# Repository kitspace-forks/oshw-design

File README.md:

###Open-source hardware design
----------

####Introduction

This repository will contain all the hardware designs by @kennethlimcp.

Temporary project name: **One oshw project per month**

The purpose is to encourage people to **embrace openness** and get more people **interested** in hardware design/hacking.

####Source-tree

Designs here are uploaded with the following document to **minimize friction** for a beginner to get started:

- Schematic design (EAGLE CAD)

- GERBER file      (fabricate PCB immediately)

- BOM list         (widely available parts + changelog)

- PDF capture      (learn without Schematic software)

- Datasheet        (easy reference without searching)

- Appnote          (deeper learning and understanding)

- Casing           (more user-friendly and safe to hold)

####Useful writeups (by me)

- [Bringing up a new board from scratch](/Resources/bring-up.md)
- [Checking a new PCB and populating it](/Resources/pcb-checks.md)
- [EAGLE start off and mistakes](/Resources/eagle-notes.md)

####Resources

- [Spark Proto2Prod website](http://www.proto2prod.com/)

- [EAGLE Help](http://web.mit.edu/xavid/arch/i386_rhel4/help/index.htm)

- [Sparkfun EAGLE Settings](https://github.com/sparkfun/SparkFun_Eagle_Settings)

- [3D Board viewer](http://3dbrdviewer.cytec.bg/)

- [KiCad Software](http://www.kicad-pcb.org/)

- [Systematic PCB verification](https://engineering.purdue.edu/ece477/Resources/SystematicPCBVerification.pdf)

- [7 fatal pcb mistakes to avoid by Make](http://makezine.com/2016/08/15/7-fatal-mistakes-avoid-printed-circuit-board-pcb-design/)

- [ Board Level
Electromagnetic Compatibility](http://www.nxp.com/files/microcontrollers/doc/app_note/AN2321.pdf)

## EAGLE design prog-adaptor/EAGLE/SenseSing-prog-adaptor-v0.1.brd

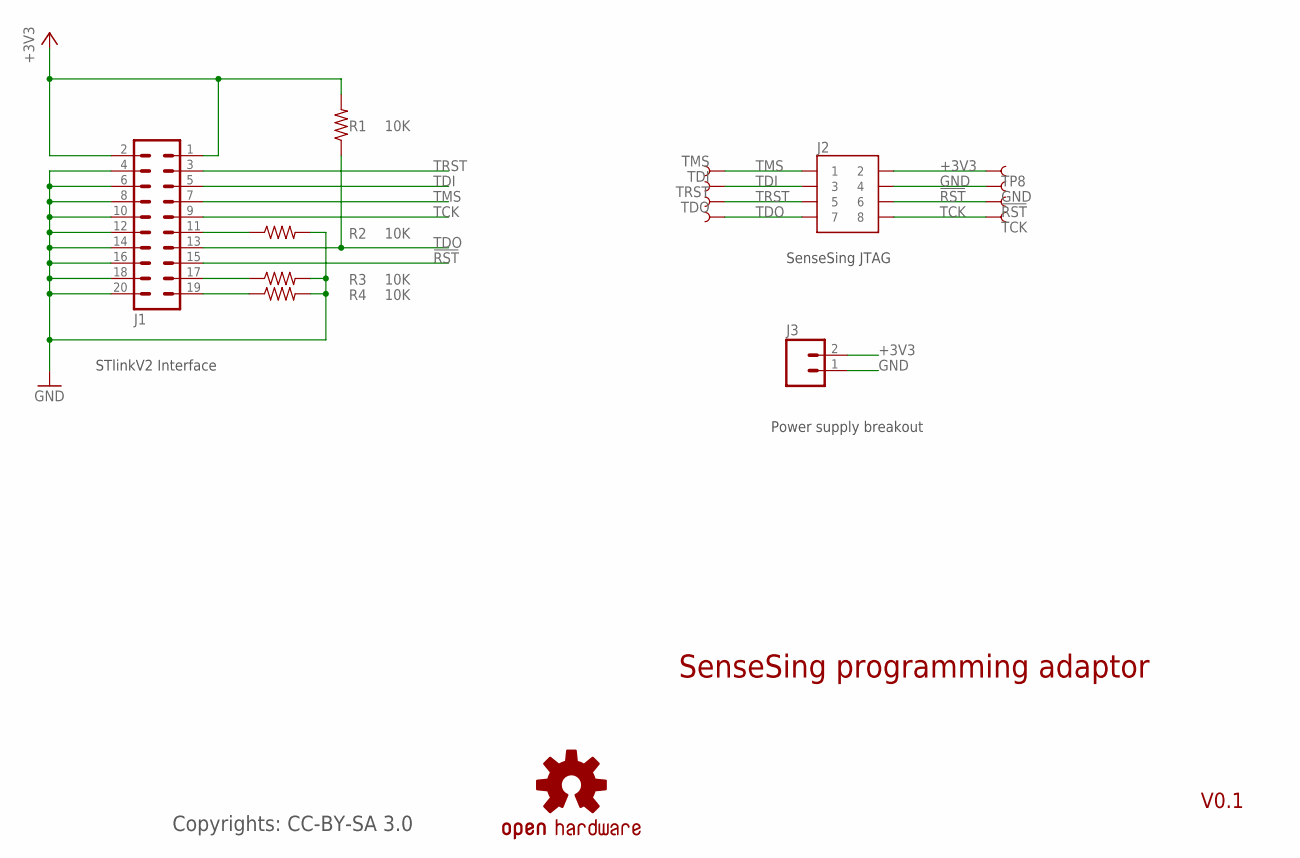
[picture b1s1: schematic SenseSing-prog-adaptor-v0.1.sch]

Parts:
!RST: TEST-POINT3; PAD.03X.03
GND: TEST-POINT3; PAD.03X.03
J1: ML20
J2: JTAG_CONNECTOR; JTAG_DIP
J3: M02PTH; 1X02
LOGO1: OSHW-LOGOPAD; OSHW-LOGO-M-PAD
R1, R2, R3, R4: 10K; AXIAL-0.3
TCK: TEST-POINT3; PAD.03X.03
TDI: TEST-POINT3; PAD.03X.03
TDO: TEST-POINT3; PAD.03X.03
TMS: TEST-POINT3; PAD.03X.03
TP8: TEST-POINT3; PAD.03X.03
TRST: TEST-POINT3; PAD.03X.03

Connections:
!RST: !RST.P$1, J1.15, J2.6
+3V3: J1.1, J1.2, J2.2, J3.2, R1.P$2 (2), TP8.P$1
GND: GND.P$1, J1.4, J1.6, J1.8, J1.10, J1.12, J1.14, J1.16, J1.18, J1.20, J2.4, J3.1, R2.P$2 (2), R3.P$2 (2), R4.P$2 (2)
unnamed: J1.19, R4.P$1 (1)
unnamed: J1.17, R3.P$1 (1)
unnamed: J1.11, R2.P$1 (1)
TCK: J1.9, J2.8, TCK.P$1
TDI: J1.5, J2.3, TDI.P$1
TDO: J1.13, J2.7, R1.P$1 (1), TDO.P$1
TMS: J1.7, J2.1, TMS.P$1
TRST: J1.3, J2.5, TRST.P$1

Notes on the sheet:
STlinkV2 Interface
SenseSing JTAG
SenseSing programming adaptor
Copyrights: CC-BY-SA 3.0
Power supply breakout

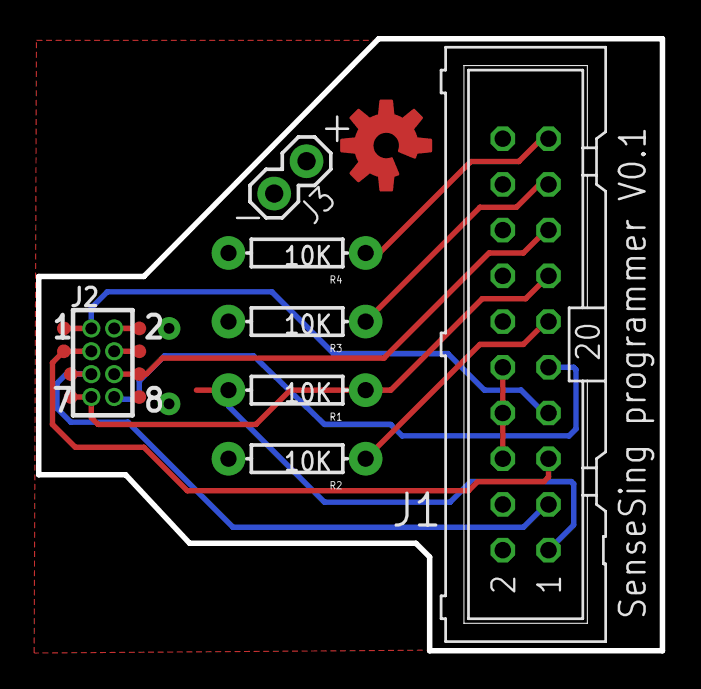
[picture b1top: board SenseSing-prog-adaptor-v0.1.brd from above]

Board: 4 copper layers, 34.7 x 34.0 mm, 16 parts (0 on the bottom side), 11 nets.

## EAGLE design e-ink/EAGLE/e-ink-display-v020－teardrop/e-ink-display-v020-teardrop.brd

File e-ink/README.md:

#Wifi E-ink display
----------

###Introduction

The main motivation for this device comes from the regular use of 16x2 or nokia old-style LCD display. They are nice but too small for a sizeable project that requires a simple but viewable display from a distance.

This also challenges me to try out FPC connector that i have never handled before and at the same time design an entire system comprising from power to display signal driver.

The current revision of **V0.0.3** does not work as the I2C GPIO expander is unable to toggle the control pins at `us` resolution so a re-design has to be done. **V0.1.0** is a WIP to improve **V0.0.2** but is only a WIP and is not a working board as well.

####Power system

- USB +5V or single cell Li-ion
- Battery charging and simultaneous system supply
- 3V3 buck converter for primary rail

#####Input options
- microB USB
- jumper wire (+ and -)

#####E-ink supply notes

A LT1945 DC/DC converter is powered by VBAT from the 1-cell li-ion battery to provide the +22V and -20V required for the Gate supply. The next power stage comprises of a simple LDO (LM78(79)/L15) to generate +15V and -15V for the Source supply. There's a LTSPICE file available in this repository that shows the performance of the LT1945 through simulation. This design comes from the datasheet and the components have been properly sized to have beefy ratings.

There are newer ICs in the market that handles the entire power generation required to drive an e-ink display and they should be utilized in the new revision if they can be bought easily in the market. Otherwise, replacing the LDOs might be a considering to achieve better low power consumption in sleep mode.

VDD and VSS supply for the e-ink is powered using a GPIO as the current draw (according to the notes) is only 1mA and this allows up to turn off the display for power saving.

The SMPS power input is controlled using a simple P-channel Mosfet load switch technique to cut off supply when it is not required.

#####Battery power management design

After much sourcing and finding a part available in the Chinese market, I found the BQ24075 suitable for the job that provides a good mix of features. This IC allows a maximum input voltage of 28V and comes with over-voltage protection! No external inductor is required (compared to BQ24260). There's also 2 status signal that allows the MCU to know if there's an external power source connected and whether the battery is currently charging. This allows us to change the "power mode" of the device with faster go-to-sleep timing when there is not power source attached.

This addition low-cost circuit footprint is added for variety. A MCP7381T is used to charge a single cell Li-ion and the VBAT is directly fed to the system. This, however, does not allow the system to be powered up if a battery is not present.

####Driver design notes

The e-ink display requires a fair bit of control pins and part of the reason is not fully understanding which pins are in use and necessary for driving. Therefore, to ensure a higher success rate during rev. 0.0.2, consideration is made to hook up all the exposed pins. Pins that are pulled high and low are also wired up with 0 ohm resistors for flexibility to test their purpose or change the pull voltage.

One design considered is to use 2 x 8 GPIO expander; one for the 8 bit data and another for the seldom toggled controls pins. There are 16 port GPIO expander in the market but having the data pins and control pins independent of each other during writes prevents accidental toggling of the incorrect pin that may result in a damaged display.

Another design is to use a separate MCU that connects directly to all the pins available but most of the Arduino options have low FLASH and RAM. The next notch up would result coding in C (MCU running some RTOS) which is too much to handle at this point in time.

The GPIO expander design is implemented for the initial rev to bring up the board with a Spark Core/Photon that is a beefier Arduino variant that allows us to avoid the low level path for now. Using an external MCU would definitely be a better path to take in future revisions. INT pins are not wired up as all the pins are used as OUTPUT.

####Peripherals

These are implemented in rev 0.0.2:

- Accelerometer to determine screen orientation
- Temperature sensor, duh
- microSD card

future considerations:

- Gyrosensor (why?)
- BLE module (good for proximity control)
- light sensor for ambience detection

####Casing

A laser cut casing would be great to house a useful demonstration set and avoid risk of damaging it from the hands of others!

####Future expansion

- Use e-ink display driver IC
- Add in IR touch sensing technology used in latest Kindle
- Backlight will be awesome much

####Lessons learnt

- Creating new footprints confidently (39-pin FPC connector, QFN-20)
- ULP script "bom.ulp" available to generate the BOM for a project. Makes it easier to manage the ever changing list of components
- ULP script "Unrouted" from Sparkfun will be useful instead of manually browsing through unrouted layer (but not that helpful..)
- need to turn on `STOP` for vias to be exposed without soldermasking
- Forgotten about teardrop ULP
- increase isolate for polygons to 0.012". Sparkfun says that would result in better yield instead of possible short
- it seems like we need to turn on the layers of concern during DRC or it will be missed out. Some silkscreen labels were "violating" some pads/vias and went unnoticed

**v0.0.2**

- need to add thermal vias for battery management IC
- updated battery related ICs label with additional "0" prefix (U01B, U02B, U03B, U04B, U05B)
- `SMPS_CTRL` pin for the LT1945 can only work without populating R12B as the GPIO port on the expander cannot be configured as an open drain to support the pull-up resistor. Have to set in code to use internal pull-up instead. Will need to consider adding an SOT-23 NPN transistor to control the on/off.
- BQ24072/3/4 might better with lower OUT voltage for next stage +3V3 step down
- Use 2K Ohm for R08B to set ILIM for BQ24075
- missed out "insert here" label for J02S
- SJ1 solder jumper can be smaller
- keepout for U03M needs to be included in the design consideration and GERBER generation
- changed OSHW logo to customized for it to be an exposed shiny silver logo :)
- made "SG 50" font a vector, 20% ratio
- incorrect J02M label, was flipped

- spaced out components to be more hand-solderable
- extend the USB pads to be more hand-solderable
- added slide switch
- RST for MCP23008-E needs to be externally biased
- R0xx should be wired to +3V3 instead of EINK_VDD
- some issue with +20v where voltage is present even when disabled

####Resources

Understanding the wiring for e-ink display would not be possible with the information shared by two pro open-source gentlemen.

- [essential scrap](http://www.essentialscrap.com/eink/index.html)
- [SpriteMods](http://spritesmods.com/?art=einkdisplay)
- [Ti Dev board](http://www.ti.com/tool/TIDM-LPBP-EPAPER)
- [SSD1606 driver](http://www.lcd-module.de/fileadmin/eng/pdf/zubehoer/ssd1606_1_1.pdf)
- [OnSemi driver](http://www.onsemi.com/pub_link/Collateral/ENA2223-D.PDF)
- [Eink reseach paper](http://aoe.scnu.edu.cn/uploadfile/2014/0508/20140508112156532.pdf)
- [STM32L0 discovery board](http://www.st.com/st-web-ui/static/active/en/resource/technical/document/user_manual/DM00118944.pdf)
- [Pebble Time teardown](https://www.ifixit.com/Teardown/Pebble+Time+Teardown/42382)
- [Pebble Watch teardown](https://www.ifixit.com/Teardown/Pebble+Teardown/13319)
- [RePaper code](https://github.com/repaper/gratis)
- [Freescale i.MX50](http://cache.freescale.com/files/32bit/doc/data_sheet/IMX50CEC.pdf)
- [GDE021A1 display project](http://www.jsykora.info/2014/06/epd-display-working/)
- [Amazon Kindle source code](http://www.amazon.com/gp/help/customer/display.html?nodeId=200203720)
- [E-ink display](http://www.buy-lcd.com/index.php?route=product/category&path=2897)
- http://www.eevblog.com/forum/microcontrollers/interfacing-epd-(e-ink)-display-from-kindle-anyone-tried
- [EPSON controller module](http://www.mouser.com/catalog/specsheets/x93ac002_f01__(S4E5B001B00A00_Product_Brief_Rev_1.0)[1].pdf)
- [Epaper shield](http://epapershield.com/index.htm)

- [PVI docs](http://wenku.baidu.com/view/c54385ea6294dd88d0d26b94.html)
- [Epson ppt](http://wenku.baidu.com/view/e451453567ec102de2bd8908.html)

Appnote

- MOSFETS in load switch applications(AND9093D)
- Reverse current/battery protection circuit (SLVA139)
- Resistor decade table (dectable)
- [USB disconnect circuit](https://developer.mbed.org/media/uploads/chris/mbed-005.1.pdf)
- [I2C resistor calculation](http://www.ti.com/lit/an/slva689/slva689.pdf)

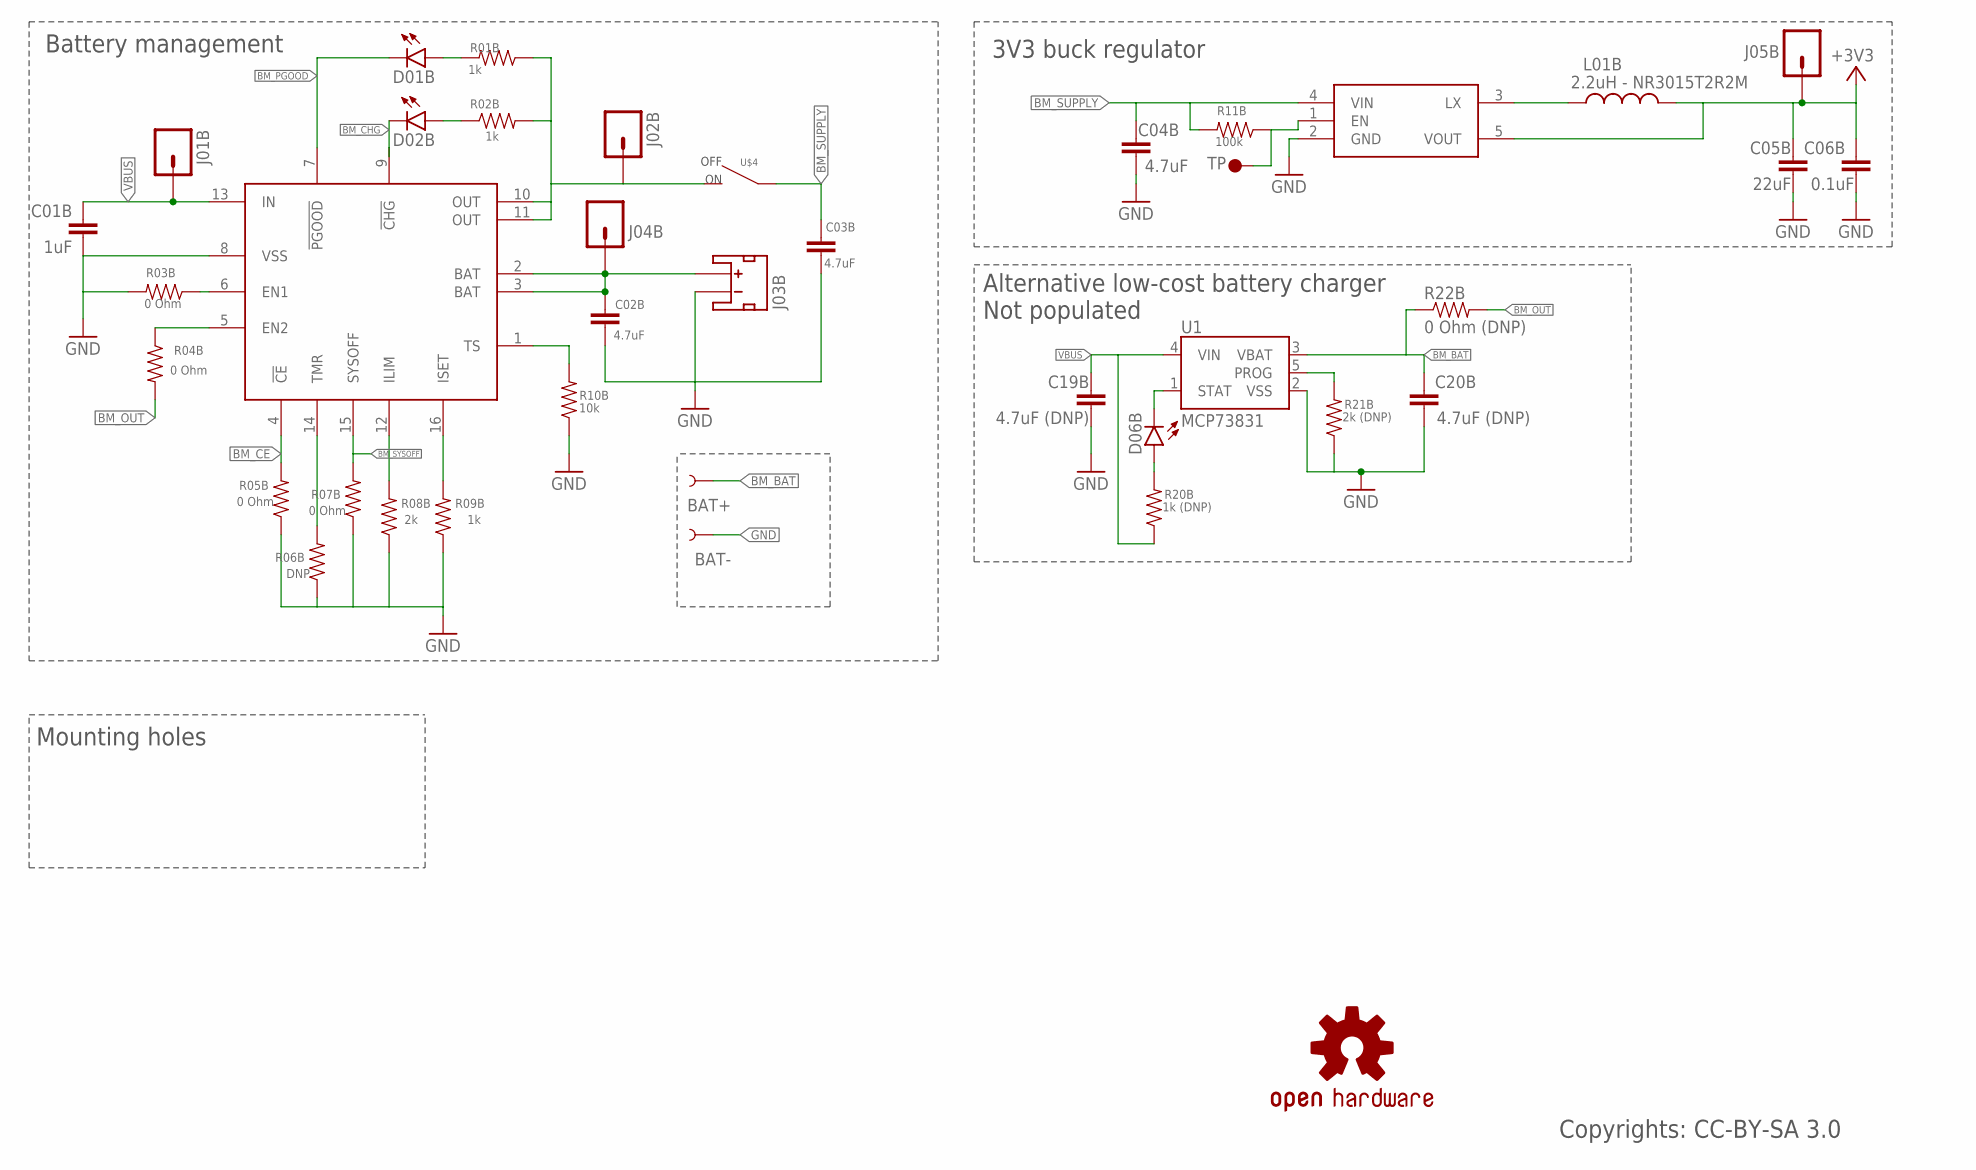
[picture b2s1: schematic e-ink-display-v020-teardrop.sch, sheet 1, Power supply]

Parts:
BAT+: TEST-POINTBOTH_SQ; TP_15_BOTH-SQ
BAT-: TEST-POINTBOTHBOTH; TP_15_BOTH
C01B: 1uF; 0603-CAP
C02B, C03B, C04B: 4.7uF; 0603-CAP
C05B: 22uF; 0603-CAP
C06B: 0.1uF; 0603-CAP
C19B, C20B: 4.7uF (DNP); 0603-CAP
D01B, D02B, D06B: LED0603; LED-0603
J01B, J02B, J04B, J05B: M01PTH; 1X01
J03B: JST_2MM_MALE; JST-2-SMD
L01B: 2.2uH - NR3015T2R2M; INDUCTOR-NR3015
LOGO1: OSHW-LOGOPAD; OSHW-LOGO-M-PAD
R01B, R02B, R09B: 1k; 0603-RES
R03B, R04B, R05B, R07B: 0 Ohm; 0603-RES
R06B: DNP; 0603-RES
R08B: 2k; 0603-RES
R10B: 10k; 0603-RES
R11B: 100k; 0603-RES
R20B: 1k (DNP); 0603-RES
R21B: 2k (DNP); 0603-RES
R22B: 0 Ohm (DNP); 1206
TP01B: TP1; TP35_BOT
U1: MCP73831; SOT23-5
U01B: BQ24075; PVQFN-16
U02B: R8008-33; SOT23-5
U$4: SWITCHSLIDE; CHANGE_OVER_SLIDE

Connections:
+3V3: C05B.2, C06B.2, J05B.1, L01B.2, U02B.5 (VOUT); also elsewhere on the board
BM_BAT: BAT+.P$1, C02B.2, C20B.2, J03B.2 (+), J04B.1, R22B.1, U1.3 (VBAT), U01B.2 (BAT), U01B.3 (BAT)
BM_CE: R05B.2, U01B.4 (!CE)
BM_CHG: D02B.C, U01B.9 (!CHG); also elsewhere on the board
BM_OUT: J02B.1, R01B.1, R02B.2, R04B.2, R22B.2, U01B.10 (OUT), U01B.11 (OUT), U$4.2
BM_PGOOD: D01B.C, U01B.7 (!PGOOD); also elsewhere on the board
BM_SUPPLY: C03B.2, C04B.2, R11B.2, U02B.4 (VIN), U$4.1; also elsewhere on the board
BM_SYSOFF: R07B.2, U01B.15 (SYSOFF)
GND: BAT-.P$1, C01B.1, C02B.1, C03B.1, C04B.1, C05B.1, C06B.1, C19B.1, C20B.1, J03B.1 (-), R03B.2, R05B.1, R06B.1, R07B.1, R08B.1, R09B.1, R10B.1, R21B.1, U1.2 (VSS), U01B.8 (VSS), U02B.2 (GND); also elsewhere on the board
unnamed: R08B.2, U01B.12 (ILIM)
unnamed: R09B.2, U01B.16 (ISET)
unnamed: R04B.1, U01B.5 (EN2)
unnamed: R03B.1, U01B.6 (EN1)
unnamed: R06B.2, U01B.14 (TMR)
unnamed: R10B.2, U01B.1 (TS)
unnamed: D02B.A, R02B.1
unnamed: D01B.A, R01B.2
unnamed: R21B.2, U1.5 (PROG)
unnamed: R11B.1, TP01B.P$1, U02B.1 (EN)
unnamed: L01B.1, U02B.3 (LX)
unnamed: D06B.C, U1.1 (STAT)
unnamed: D06B.A, R20B.2
VBUS: C01B.2, C19B.2, J01B.1, R20B.1, U1.4 (VIN), U01B.13 (IN); also elsewhere on the board

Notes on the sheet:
Battery management
3V3 buck regulator
Mounting holes
Alternative low-cost battery charger Not populated
Copyrights: CC-BY-SA 3.0

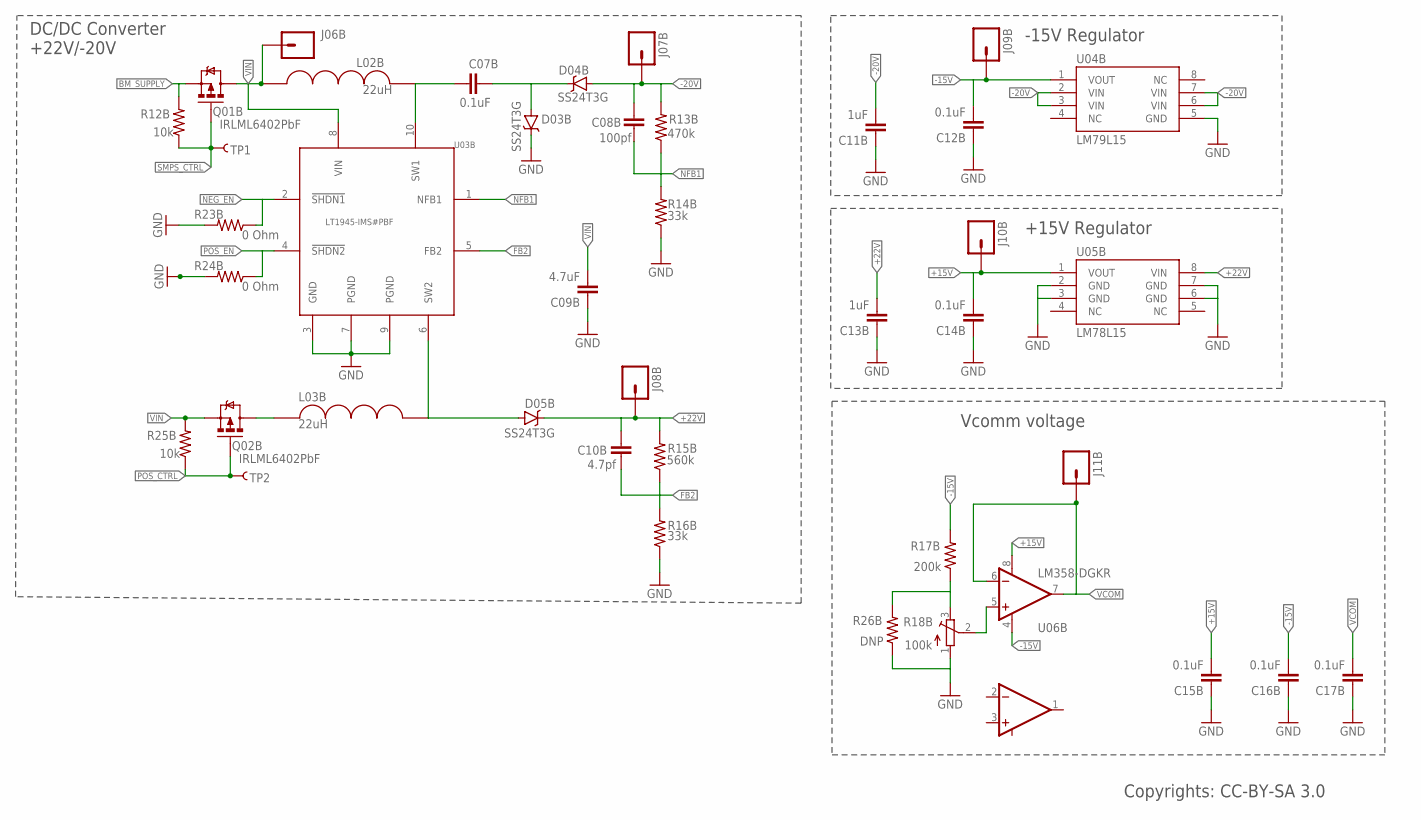
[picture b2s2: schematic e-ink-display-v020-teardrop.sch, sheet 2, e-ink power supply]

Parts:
C07B, C12B, C14B, C15B, C16B, C17B: 0.1uF; 0603-CAP
C08B: 100pf; 0603-CAP
C09B: 4.7uF; 0603-CAP
C10B: 4.7pf; 0603-CAP
C11B, C13B: 1uF; 0603-CAP
D03B, D04B, D05B: SS24T3G; SMA-DIODE
J06B, J07B, J08B, J09B, J10B, J11B: M01PTH; 1X01
L02B, L03B: 22uH; 4040(1515)
Q01B, Q02B: IRLML6402PbF; SOT23-3
R12B, R25B: 10k; 0603-RES
R13B: 470k; 0603-RES
R14B, R16B: 33k; 0603-RES
R15B: 560k; 0603-RES
R17B: 200k; 0603-RES
R18B: 100k; TC33X
R23B, R24B: 0 Ohm; 0603-RES
R26B: DNP; 0603-RES
TP1, TP2: TEST-POINTBOTHBOTH; TP_15_BOTH
U03B: LT1945-IMS#PBF; MSOP-10
U04B: LM79L15; SO08
U05B: LM78L15; SO08
U06B: LM358-DGKR; MSOP-8

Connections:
+15V: C14B.2, C15B.2, J10B.1, U05B.1 (VOUT), U06B.8 (V+); also elsewhere on the board
+22V: C10B.2, C13B.2, D05B.C, J08B.1, R15B.2, U05B.8 (VIN); also elsewhere on the board
-15V: C12B.2, C16B.2, J09B.1, R17B.2, U04B.1 (VOUT), U06B.4 (V-); also elsewhere on the board
-20V: C08B.2, C11B.2, D04B.A, J07B.1, R13B.2, U04B.2 (VIN), U04B.3 (VIN), U04B.6 (VIN), U04B.7 (VIN); also elsewhere on the board
BM_SUPPLY: Q01B.2 (S), R12B.2; also elsewhere on the board
FB2: C10B.1, R15B.1, R16B.2, U03B.5 (FB2)
GND: C09B.1, C11B.1, C12B.1, C13B.1, C14B.1, C15B.1, C16B.1, C17B.1, D03B.C, R14B.1, R16B.1, R18B.1 (A), R23B.2, R24B.2, R26B.1, U03B.3 (GND), U03B.7 (PGND), U03B.9 (PGND), U04B.5 (GND), U05B.2 (GND), U05B.3 (GND), U05B.6 (GND), U05B.7 (GND); also elsewhere on the board
unnamed: C07B.1, L02B.P$2, U03B.10 (SW1)
unnamed: C07B.2, D03B.A, D04B.C
unnamed: R18B.2 (S), U06B.5 (+IN2)
unnamed: D05B.A, L03B.P$2, U03B.6 (SW2)
unnamed: L03B.P$1, Q02B.3 (D)
unnamed: R17B.1, R18B.3 (E), R26B.2
NEG_EN: R23B.1, U03B.2 (!SHDN1); also elsewhere on the board
NFB1: C08B.1, R13B.1, R14B.2, U03B.1 (NFB1)
POS_CTRL: Q02B.1 (G), R25B.1, TP2.P$1; also elsewhere on the board
POS_EN: R24B.1, U03B.4 (!SHDN2); also elsewhere on the board
SMPS_CTRL: Q01B.1 (G), R12B.1, TP1.P$1; also elsewhere on the board
VCOM: C17B.2, J11B.1, U06B.6 (-IN2), U06B.7 (OUT2); also elsewhere on the board
VIN: C09B.2, J06B.1, L02B.P$1, Q01B.3 (D), Q02B.2 (S), R25B.2, U03B.8 (VIN)

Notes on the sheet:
-15V Regulator
+15V Regulator
Vcomm voltage
DC/DC Converter +22V/-20V
Copyrights: CC-BY-SA 3.0

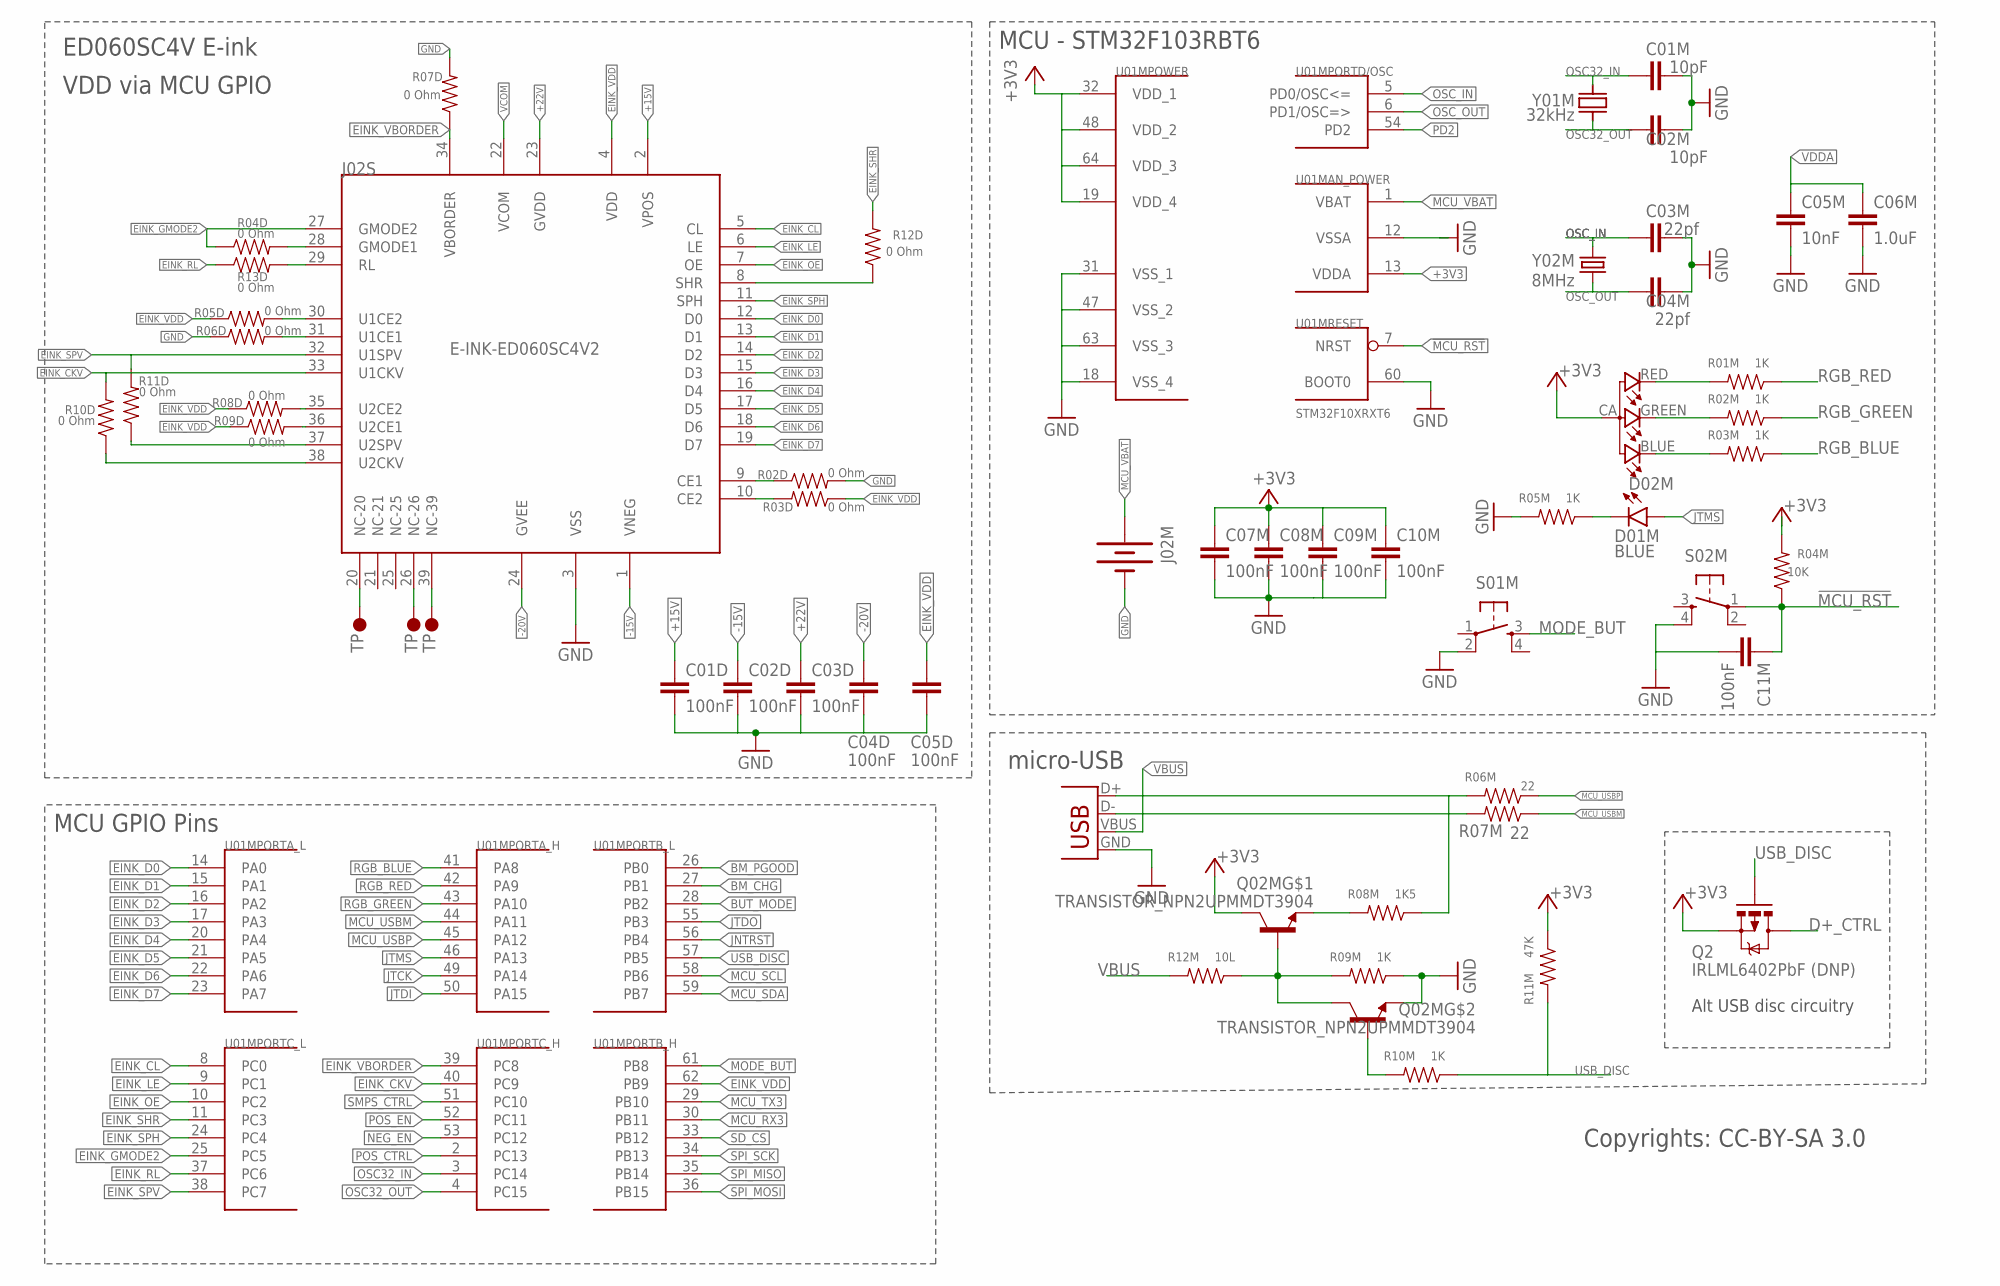
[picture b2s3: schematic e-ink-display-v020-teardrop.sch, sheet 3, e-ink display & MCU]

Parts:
C01D, C02D, C03D, C04D, C05D, C07M, C08M, C09M, C10M, C11M: 100nF; 0603-CAP
C01M, C02M: 10pF; 0603-CAP
C03M, C04M: 22pf; 0603-CAP
C05M: 10nF; 0603-CAP
C06M: 1.0uF; 0603-CAP
D01M: BLUE; LED-0603
D02M: RGB-LED-CLMVB-FKARGB; PLCC4-2MM-RGB
J01M: USBUSB-MICROB-PAD-EXTEND; USB-MICROB-SLOT-HOLE-EXTEND
J02M: BATTERY20PTH; BATTCOM_20MM_PTH
J02S: E-INK-ED060SC4V2; FPC-0.3-39
Q2: IRLML6402PbF (DNP); SOT23-3
Q02M: TRANSISTOR_NPN2UPMMDT3904; SOT363
R01M, R02M, R03M, R05M, R09M, R10M: 1K; 0603-RES
R02D, R03D, R04D, R05D, R06D, R07D, R08D, R09D, R10D, R11D, R12D, R13D: 0 Ohm; 0603-RES
R04M: 10K; 0603-RES
R06M, R07M: 22; 0603-RES
R08M: 1K5; 0603-RES
R11M: 47K; 0603-RES
R12M: 10L; 0603-RES
S01M, S02M: TAC_SWITCHSMD; TACTILE_SWITCH_SMD
U01M: STM32F10XRXT6; TQFP64
U$1, U$8, U$9: TP1; TP35_BOT
Y01M: 32kHz; FC135
Y02M: 8MHz; CRYSTAL-SMD-5X3

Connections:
!MCU_RST: C11M.1, R04M.1, S02M.1, U01M.7 (NRST); also elsewhere on the board
+3V3: C07M.1, C08M.1, C09M.1, C10M.1, D02M.CA (1), Q2.2 (S), Q02M.6 (C), R04M.2, R11M.1, U01M.13 (VDDA), U01M.19 (VDD_4), U01M.32 (VDD_1), U01M.48 (VDD_2), U01M.64 (VDD_3); also elsewhere on the board
+15V: C01D.1, J02S.2 (VPOS); also elsewhere on the board
+22V: C03D.1, J02S.23 (GVDD); also elsewhere on the board
-15V: C02D.1, J02S.1 (VNEG); also elsewhere on the board
-20V: C04D.1, J02S.24 (GVEE); also elsewhere on the board
BM_CHG: U01M.27 (PB1); also elsewhere on the board
BM_PGOOD: U01M.26 (PB0); also elsewhere on the board
BUT_MODE: U01M.28 (PB2)
CE2: J02S.10 (CE2), R03D.2
D+_CTRL: Q2.3 (D), Q02M.1 (E), R08M.2
EINK_CKV: J02S.33 (U1CKV), R10D.2, U01M.40 (PC9); also elsewhere on the board
EINK_CL: J02S.5 (CL), U01M.8 (PC0); also elsewhere on the board
EINK_D0: J02S.12 (D0), U01M.14 (PA0); also elsewhere on the board
EINK_D1: J02S.13 (D1), U01M.15 (PA1); also elsewhere on the board
EINK_D2: J02S.14 (D2), U01M.16 (PA2); also elsewhere on the board
EINK_D3: J02S.15 (D3), U01M.17 (PA3); also elsewhere on the board
EINK_D4: J02S.16 (D4), U01M.20 (PA4); also elsewhere on the board
EINK_D5: J02S.17 (D5), U01M.21 (PA5); also elsewhere on the board
EINK_D6: J02S.18 (D6), U01M.22 (PA6); also elsewhere on the board
EINK_D7: J02S.19 (D7), U01M.23 (PA7); also elsewhere on the board
EINK_GMODE2: J02S.27 (GMODE2), R04D.1, U01M.25 (PC5); also elsewhere on the board
EINK_LE: J02S.6 (LE), U01M.9 (PC1); also elsewhere on the board
EINK_OE: J02S.7 (OE), U01M.10 (PC2); also elsewhere on the board
EINK_RL: R13D.1, U01M.37 (PC6); also elsewhere on the board
EINK_SHR: R12D.2, U01M.11 (PC3); also elsewhere on the board
EINK_SPH: J02S.11 (SPH), U01M.24 (PC4); also elsewhere on the board
EINK_SPV: J02S.32 (U1SPV), R11D.2, U01M.38 (PC7); also elsewhere on the board
EINK_VBORDER: J02S.34 (VBORDER), R07D.1, U01M.39 (PC8); also elsewhere on the board
EINK_VDD: C05D.1, J02S.4 (VDD), R03D.1, R05D.1, R08D.1, R09D.1, U01M.62 (PB9); also elsewhere on the board
GND: C01D.2, C01M.2, C02D.2, C02M.2, C03D.2, C03M.2, C04D.2, C04M.2, C05D.2, C05M.2, C06M.2, C07M.2, C08M.2, C09M.2, C10M.2, C11M.2, J01M.GND, J02M.2 (-), J02S.3 (VSS), Q02M.4 (E), R02D.2, R05M.2, R06D.1, R07D.2, R09M.1, S01M.2, S02M.4, U01M.12 (VSSA), U01M.18 (VSS_4), U01M.31 (VSS_1), U01M.47 (VSS_2), U01M.60 (BOOT0), U01M.63 (VSS_3); also elsewhere on the board
JNTRST: U01M.56 (PB4); also elsewhere on the board
JTCK: U01M.49 (PA14); also elsewhere on the board
JTDI: U01M.50 (PA15); also elsewhere on the board
JTDO: U01M.55 (PB3); also elsewhere on the board
JTMS: D01M.A, U01M.46 (PA13); also elsewhere on the board
MCU_RX3: U01M.30 (PB11); also elsewhere on the board
MCU_SCL: U01M.58 (PB6); also elsewhere on the board
MCU_SDA: U01M.59 (PB7); also elsewhere on the board
MCU_TX3: U01M.29 (PB10); also elsewhere on the board
MCU_USBM: R07M.1, U01M.44 (PA11)
MCU_USBP: R06M.1, U01M.45 (PA12)
MCU_VBAT: J02M.1 (+), U01M.1 (VBAT)
MODE_BUT: S01M.3, U01M.61 (PB8)
N$: J01M.D+, R06M.2, R08M.1
unnamed: J02S.28 (GMODE1), R04D.2
unnamed: J02S.31 (U1CE1), R06D.2
unnamed: D02M.RED (4), R01M.2
unnamed: Q02M.2 (B), Q02M.3 (C), R09M.2, R12M.1
unnamed: J02S.29 (RL), R13D.2
unnamed: J02S.35 (U2CE2), R08D.2
unnamed: J02S.36 (U2CE1), R09D.2
unnamed: J02S.9 (CE1), R02D.1
unnamed: J02S.20 (NC-20), U$1.P$1
unnamed: J02S.26 (NC-26), U$8.P$1
unnamed: J02S.8 (SHR), R12D.1
unnamed: J02S.39 (NC-39), U$9.P$1
unnamed: Q02M.5 (B), R10M.2
unnamed: D01M.C, R05M.1
unnamed: J01M.D-, R07M.2
NEG_EN: U01M.53 (PC12); also elsewhere on the board
OSC32_IN: C01M.1, U01M.3 (PC14), Y01M.X2 (2)
OSC32_OUT: C02M.1, U01M.4 (PC15), Y01M.X1 (1)
OSC_IN: C03M.1, U01M.5 (PD0/OSC<=), Y02M.3 (2)
OSC_OUT: C04M.1, U01M.6 (PD1/OSC=>), Y02M.1
PD2: U01M.54 (PD2)
POS_CTRL: U01M.2 (PC13); also elsewhere on the board
POS_EN: U01M.52 (PC11); also elsewhere on the board
R02M: D02M.GREEN (3), R02M.2
R03M: D02M.BLUE (2), R03M.2
RGB_BLUE: R03M.1, U01M.41 (PA8)
RGB_GREEN: R02M.1, U01M.43 (PA10)
RGB_RED: R01M.1, U01M.42 (PA9)
SD_CS: U01M.33 (PB12); also elsewhere on the board
SMPS_CTRL: U01M.51 (PC10); also elsewhere on the board
SPI_MISO: U01M.35 (PB14); also elsewhere on the board
SPI_MOSI: U01M.36 (PB15); also elsewhere on the board
SPI_SCK: U01M.34 (PB13); also elsewhere on the board
U1CE2: J02S.30 (U1CE2), R05D.2
U2CKV: J02S.38 (U2CKV), R10D.1
U2SPV: J02S.37 (U2SPV), R11D.1
USB_DISC: Q2.1 (G), R10M.1, R11M.2, U01M.57 (PB5); also elsewhere on the board
VBUS: J01M.VBUS, R12M.2; also elsewhere on the board
VCOM: J02S.22 (VCOM); also elsewhere on the board
VDDA: C05M.1, C06M.1

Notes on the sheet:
ED060SC4V E-ink VDD via MCU GPIO
MCU - STM32F103RBT6
Copyrights: CC-BY-SA 3.0
micro-USB
MCU GPIO Pins
Alt USB disc circuitry

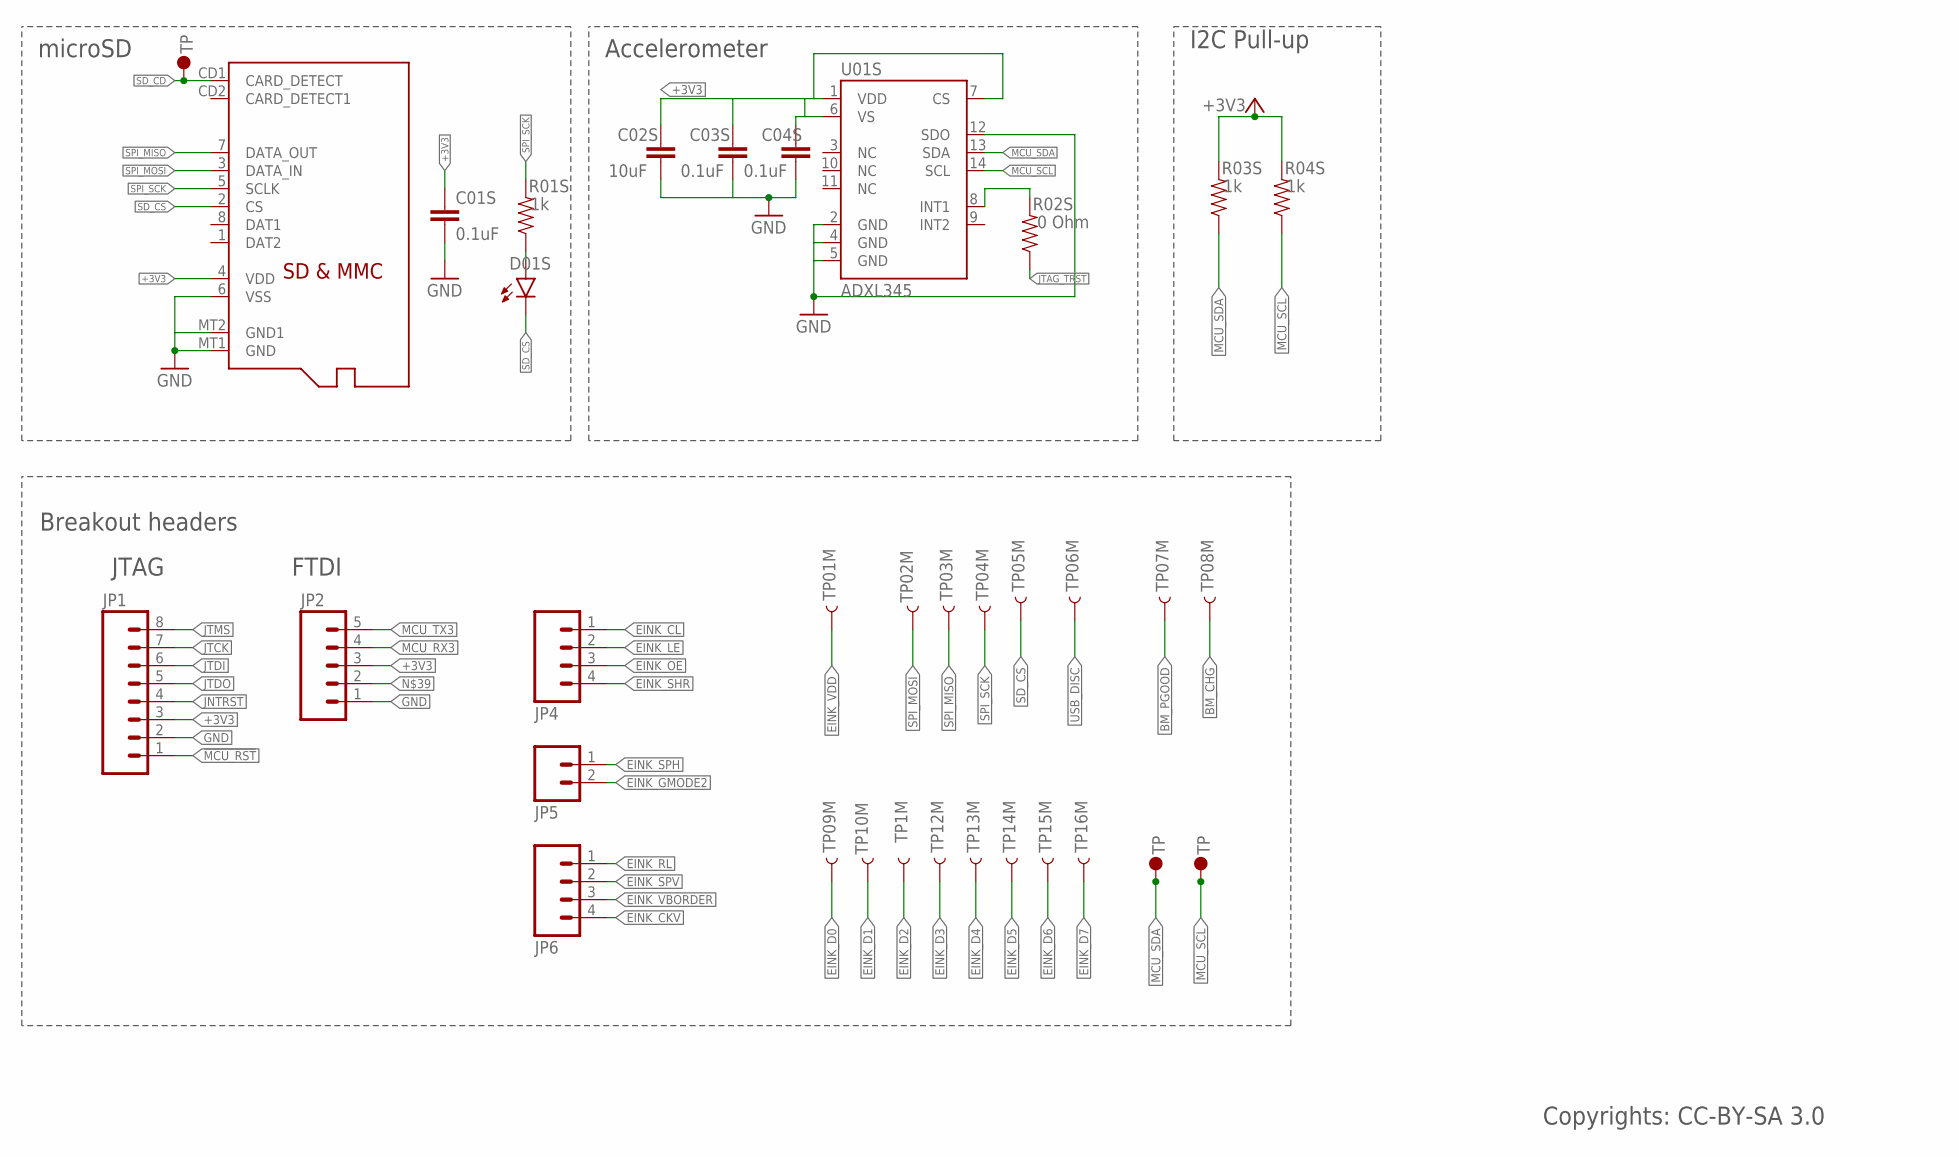
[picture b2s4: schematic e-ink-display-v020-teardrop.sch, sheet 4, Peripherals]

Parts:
C01S, C03S, C04S: 0.1uF; 0603-CAP
C02S: 10uF; 0603-CAP
D01S: LED0603; LED-0603
J01S: MICROSD
JP1: M08; 1X08_ROUND
JP2: M05PTH; 1X05
JP4, JP6: M04PTH; 1X04
JP5: M02PTH; 1X02
R01S, R03S, R04S: 1k; 0603-RES
R02S: 0 Ohm; 0603-RES
TP01M, TP1M, TP02M, TP04M, TP05M, TP06M, TP07M, TP08M, TP09M, TP10M, TP12M, TP13M, TP14M, TP15M, TP16M: TEST-POINTBOTHBOTH; TP_15_BOTH
TP03M: TEST-POINTTP_15TH_THRU; TP_15TH
TP17M, TP18M: TP1; TP35_BOT
U01S: ADXL345; LGA14
U$5: TP3; TP60_BOT

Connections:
!MCU_RST: JP1.1; also elsewhere on the board
+3V3: C01S.1, C02S.1, C03S.1, C04S.1, J01S.4 (VDD), JP1.3, JP2.3, R03S.2, R04S.2, U01S.1 (VDD), U01S.6 (VS), U01S.7 (CS); also elsewhere on the board
BM_CHG: TP08M.P$1; also elsewhere on the board
BM_PGOOD: TP07M.P$1; also elsewhere on the board
EINK_CKV: JP6.4; also elsewhere on the board
EINK_CL: JP4.1; also elsewhere on the board
EINK_D0: TP09M.P$1; also elsewhere on the board
EINK_D1: TP10M.P$1; also elsewhere on the board
EINK_D2: TP1M.P$1; also elsewhere on the board
EINK_D3: TP12M.P$1; also elsewhere on the board
EINK_D4: TP13M.P$1; also elsewhere on the board
EINK_D5: TP14M.P$1; also elsewhere on the board
EINK_D6: TP15M.P$1; also elsewhere on the board
EINK_D7: TP16M.P$1; also elsewhere on the board
EINK_GMODE2: JP5.2; also elsewhere on the board
EINK_LE: JP4.2; also elsewhere on the board
EINK_OE: JP4.3; also elsewhere on the board
EINK_RL: JP6.1; also elsewhere on the board
EINK_SHR: JP4.4; also elsewhere on the board
EINK_SPH: JP5.1; also elsewhere on the board
EINK_SPV: JP6.2; also elsewhere on the board
EINK_VBORDER: JP6.3; also elsewhere on the board
EINK_VDD: TP01M.P$1; also elsewhere on the board
GND: C01S.2, C02S.2, C03S.2, C04S.2, J01S.6 (VSS), J01S.MT1 (GND), J01S.MT2 (GND1), JP1.2, JP2.1, U01S.2 (GND), U01S.4 (GND), U01S.5 (GND), U01S.12 (SDO); also elsewhere on the board
JNTRST: JP1.4; also elsewhere on the board
JTAG_TRST: R02S.1
JTCK: JP1.7; also elsewhere on the board
JTDI: JP1.6; also elsewhere on the board
JTDO: JP1.5; also elsewhere on the board
JTMS: JP1.8; also elsewhere on the board
MCU_RX3: JP2.4; also elsewhere on the board
MCU_SCL: R04S.1, TP18M.P$1, U01S.14 (SCL); also elsewhere on the board
MCU_SDA: R03S.1, TP17M.P$1, U01S.13 (SDA); also elsewhere on the board
MCU_TX3: JP2.5; also elsewhere on the board
unnamed: R02S.2, U01S.8 (INT1)
R01S: D01S.A, R01S.1
SD_CD: J01S.CD1 (CARD_DETECT), U$5.P$1
SD_CS: D01S.C, J01S.2 (CS), TP05M.P$1; also elsewhere on the board
SPI_MISO: J01S.7 (DATA_OUT), TP03M.P$1; also elsewhere on the board
SPI_MOSI: J01S.3 (DATA_IN), TP02M.P$1; also elsewhere on the board
SPI_SCK: J01S.5 (SCLK), R01S.2, TP04M.P$1; also elsewhere on the board
USB_DISC: TP06M.P$1; also elsewhere on the board

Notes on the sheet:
microSD
Accelerometer
Copyrights: CC-BY-SA 3.0
I2C Pull-up
JTAG
FTDI
Breakout headers

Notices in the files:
e-ink/EAGLE/e-ink-display-v020－teardrop/e-ink-display-v020-teardrop.brd:
Apache License 2.0
parts and their libraries:
SparkFun-Capacitors: Licensing: Creative Commons ShareAlike 4.0 International - https://creativecommons.org/licenses/by-sa/4.0
SparkFun-Passives: Licensing: CC v3.0 Share-Alike You are welcome to use this library for commercial purposes.
